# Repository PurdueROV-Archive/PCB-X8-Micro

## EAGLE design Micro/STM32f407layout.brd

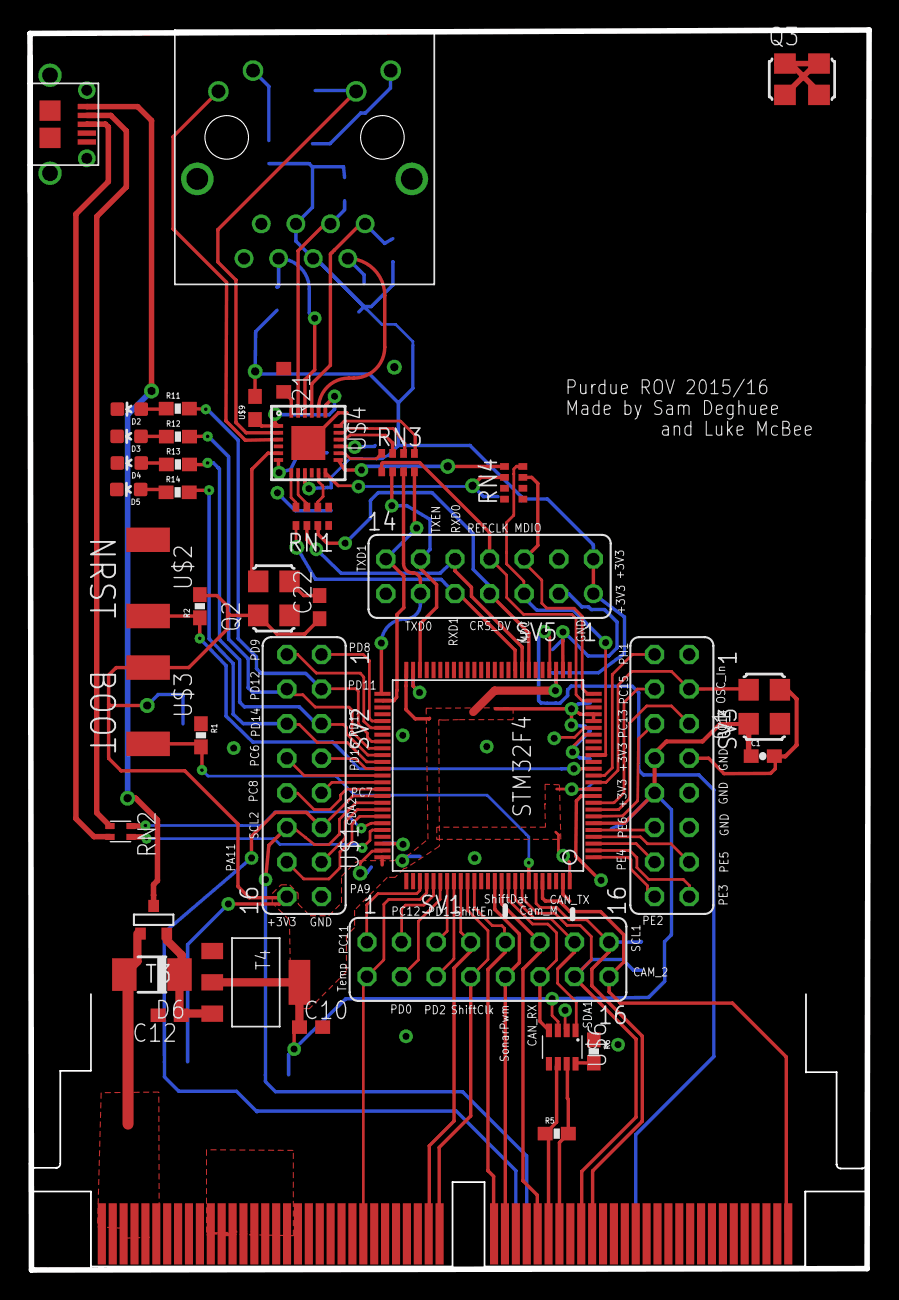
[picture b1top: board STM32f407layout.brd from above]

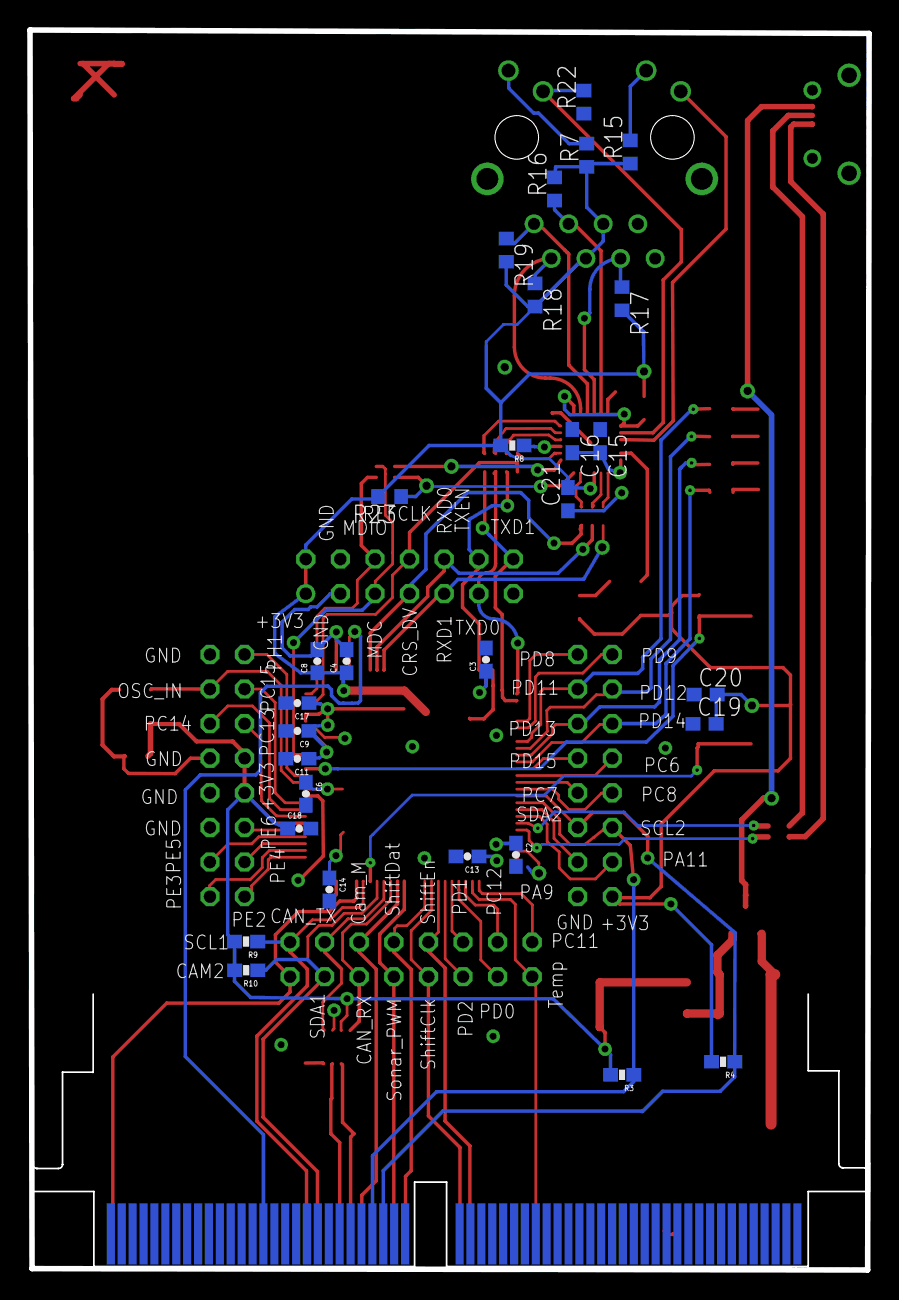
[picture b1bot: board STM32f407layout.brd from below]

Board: 2 copper layers, 61.6 x 91.0 mm, 69 parts (29 on the bottom side), 93 nets.

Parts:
C1: 0603-CAP
C2, C3: 0.22uF; 0603-CAP
C4, C6, C9, C11, C13, C14, C18: 0.1uF; 0603-CAP
C8: 4.7uF; 0603-CAP
C10, C12: 0.22uF; C0603
C15: 1uF; C0603
C16: 1nF; C0603
C17: 1uF; 0603-CAP
C19, C20, C21: 100nF; C0603
C22: 0.01uF; C0603
D2, D3, D4, D5: LED-0603
D6: DO-214AC
Q1, Q3: ASF
Q2: ASV-8; ASF
R1, R2: 10k; 0603-RES
R3, R4, R9, R10: 4.7K; 0603-RES
R5: 120; 0603-RES
R6: 100K; 0603-RES
R7, R15: 250R; R0603
R8: 10K; 0603-RES
R11, R12, R13, R14: 83; 0603-RES
R16, R17, R18, R19: 49.9R; R0603
R21: 12.1K; R0603
R22: 4.7K; R0603
R23: 1.5k; R0603
RN1, RN3, RN4: CAY16
RN2: EXBV4V
SV1, SV2, SV3: FE08-2
SV5: FE07-2
T3: FDN340P; SOT-23
T4: AP1117_LIN_REG; SOT223
U$1: STM32F4; LQFP100
U$2, U$3: SWITCH; SW_2512
U$4: LAN8720LAN8720; 24-QFN
U$5: MICROUSB; MICRO_B
U$6: MAX3051MAX3051; SOT23-8L
U$7: J00-0065NL
U$8: HSC8PART-60; HSC8-60PINOUUT
U$9: 0603

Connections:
+3V3: C1.1, C4.1, C6.1, C8.1, C9.1, C10.1, C11.1, C13.1, C14.1, C17.1, C18.1, C19.2, C20.2, C21.2, C22.1, Q1.4, Q2.4, R2.2, R3.2, R4.2, R7.1, R8.2, R9.2, R10.2, R15.1, R16.2, R17.2, R18.2, R19.2, R23.2, SV2.16, SV3.8, SV3.10, SV5.1, SV5.2, T4.TAB, T4.VOUT, U$1.P6, U$1.P11, U$1.P19, U$1.P21, U$1.P22, U$1.P28, U$1.P50, U$1.P75, U$1.P100, U$3.1, U$4.9, U$6.3, U$7.4, U$7.5, U$9.2
+5V: D6.A, T3.3, U$8.T1, U$8.T2, U$8.T3, U$8.T4, U$8.T5, U$8.T6
ALT_CAMERA_SERVO_MOTOR_PWM: SV1.16, U$1.P96, U$8.T60
BUS_SPEED: R22.2, U$4.2, U$7.10
CANH1: R5.2, U$6.7, U$8.T39
CANL1: R5.1, U$6.6, U$8.T38
CAN_RX: SV1.12, U$1.P91, U$6.4
CAN_TX: SV1.13, U$1.P92, U$6.1
CRS_DV: RN1.3, SV5.7, U$1.P32
DIFF_RD+: R16.1, U$4.23, U$7.3
DIFF_RD-: R17.1, U$4.22, U$7.6
DIFF_TD+: R19.1, U$4.21, U$7.1
DIFF_TD-: R18.1, U$4.20, U$7.2
GND: C1.2, C2.2, C3.2, C4.2, C6.2, C8.2, C9.2, C10.2, C11.2, C12.2, C13.2, C14.2, C15.1, C16.1, C17.2, C18.2, C19.1, C20.1, C21.1, C22.2, D2.C, D3.C, D4.C, D5.C, Q1.2, Q2.2, R1.1, R6.1, R21.1, R22.1, SV2.15, SV3.1, SV3.7, SV3.9, SV3.11, SV5.3, SV5.4, T4.GND, U$1.P10, U$1.P20, U$1.P27, U$1.P74, U$1.P99, U$2.1, U$4.VSS_PAD, U$5.GND1, U$5.GND2, U$5.GND3, U$5.GND4, U$5.GND7, U$5.GND8, U$5.P4, U$5.P5, U$6.2, U$7.8, U$7.15, U$7.16, U$8.T11, U$8.T12, U$8.T13, U$8.T14, U$8.T15, U$8.T16, U$8.T17, U$8.T18
GREEN: R7.2, U$7.9
I2C1_SCL: R9.1, SV1.15, U$1.P95, U$8.T42
I2C1_SDA: R10.1, SV1.14, U$1.P93, U$8.T41
I2C3_SCL: R3.1, SV2.12, U$1.P67, U$8.B36
I2C3_SDA: R4.1, SV2.11, U$1.P66, U$8.B35
LINK/ACT: U$4.3, U$7.12
MAIN_CAMERA_SERVO_MOTOR_PWM: SV1.11, U$1.P90, U$8.T37
MDC: RN4.8, SV5.5, U$1.P16
MDE: RN4.1, U$4.13
MDIO: RN4.7, SV5.6, U$1.P25
unnamed: C2.1, U$1.P73
unnamed: C3.1, U$1.P49
unnamed: R1.2, U$1.P94, U$3.2
unnamed: R2.1, U$1.P14, U$2.2
unnamed: C15.2, C16.2, U$4.6
unnamed: RN1.6, U$4.11
unnamed: R6.2, U$6.8
unnamed: RN2.1, U$5.P2
unnamed: RN3.4, U$4.14
unnamed: D3.A, R12.1
unnamed: D5.A, R14.1
unnamed: RN3.3, U$4.16
unnamed: D4.A, R13.1
unnamed: D2.A, R11.1
unnamed: RN3.2, U$4.17
unnamed: RN3.1, U$4.18
unnamed: U$4.1, U$4.19, U$9.1
unnamed: R21.2, U$4.24
unnamed: R23.1, RN4.2, U$4.12
unnamed: RN2.2, U$5.P3
unnamed: RN1.7, U$4.8
unnamed: RN1.8, U$4.7
unnamed: Q3.1, Q3.2, Q3.3, Q3.4
unnamed: T3.1, U$5.P1
unnamed: C12.1, D6.C, T3.2, T4.VIN
NRST: R8.1, U$4.15
OSC_IN: Q1.3, SV3.3, U$1.P12
PA9: SV2.13, U$1.P68
PA10: SV2.14, U$1.P69
PC6: SV2.8, U$1.P63
PC7: SV2.9, U$1.P64
PC8: SV2.10, U$1.P65
PC10: SV1.1, U$1.P78
PC12: SV1.3, U$1.P80
PC13: SV3.6, U$1.P7
PC14: SV3.5, U$1.P8
PC15: SV3.4, U$1.P9
PD0: SV1.4, U$1.P81
PD1: SV1.5, U$1.P82
PD2: SV1.6, U$1.P83
PD8: SV2.1, U$1.P55
PD9: SV2.2, U$1.P56
PD11: R11.2, SV2.3, U$1.P58
PD12: R12.2, SV2.4, U$1.P59
PD13: R13.2, SV2.5, U$1.P60
PD14: R14.2, SV2.6, U$1.P61
PD15: SV2.7, U$1.P62
PE2: SV3.16, U$1.P1
PE3: SV3.15, U$1.P2
PE4: SV3.14, U$1.P3
PE5: SV3.13, U$1.P4
PE6: SV3.12, U$1.P5
PH1: SV3.2, U$1.P13
REFCLK: RN3.5, SV5.8, U$1.P24
RXD0: RN1.2, SV5.10, U$1.P33
RXD1: RN1.1, SV5.9, U$1.P34
SHIFTREG_CLK: SV1.8, U$1.P85, U$8.T32
SHIFTREG_DATA: SV1.9, U$1.P86, U$8.T33
SHIFTREG_ENABLE: SV1.7, U$1.P84, U$8.T31
SONAR_DAC: U$1.P29, U$8.B46
SONAR_PWM: SV1.10, U$1.P89, U$8.T34
TEMP_BACKUP: SV1.2, U$1.P79, U$8.T25
TXD0: RN3.7, SV5.11, U$1.P51
TXD1: RN3.8, SV5.14, U$1.P52
TXEN: RN3.6, SV5.12, U$1.P48
USB_D+: RN2.3, U$1.P71
USB_D-: RN2.4, U$1.P70
XTAL1: Q2.3, U$4.5
YELLOW: R15.2, U$7.11

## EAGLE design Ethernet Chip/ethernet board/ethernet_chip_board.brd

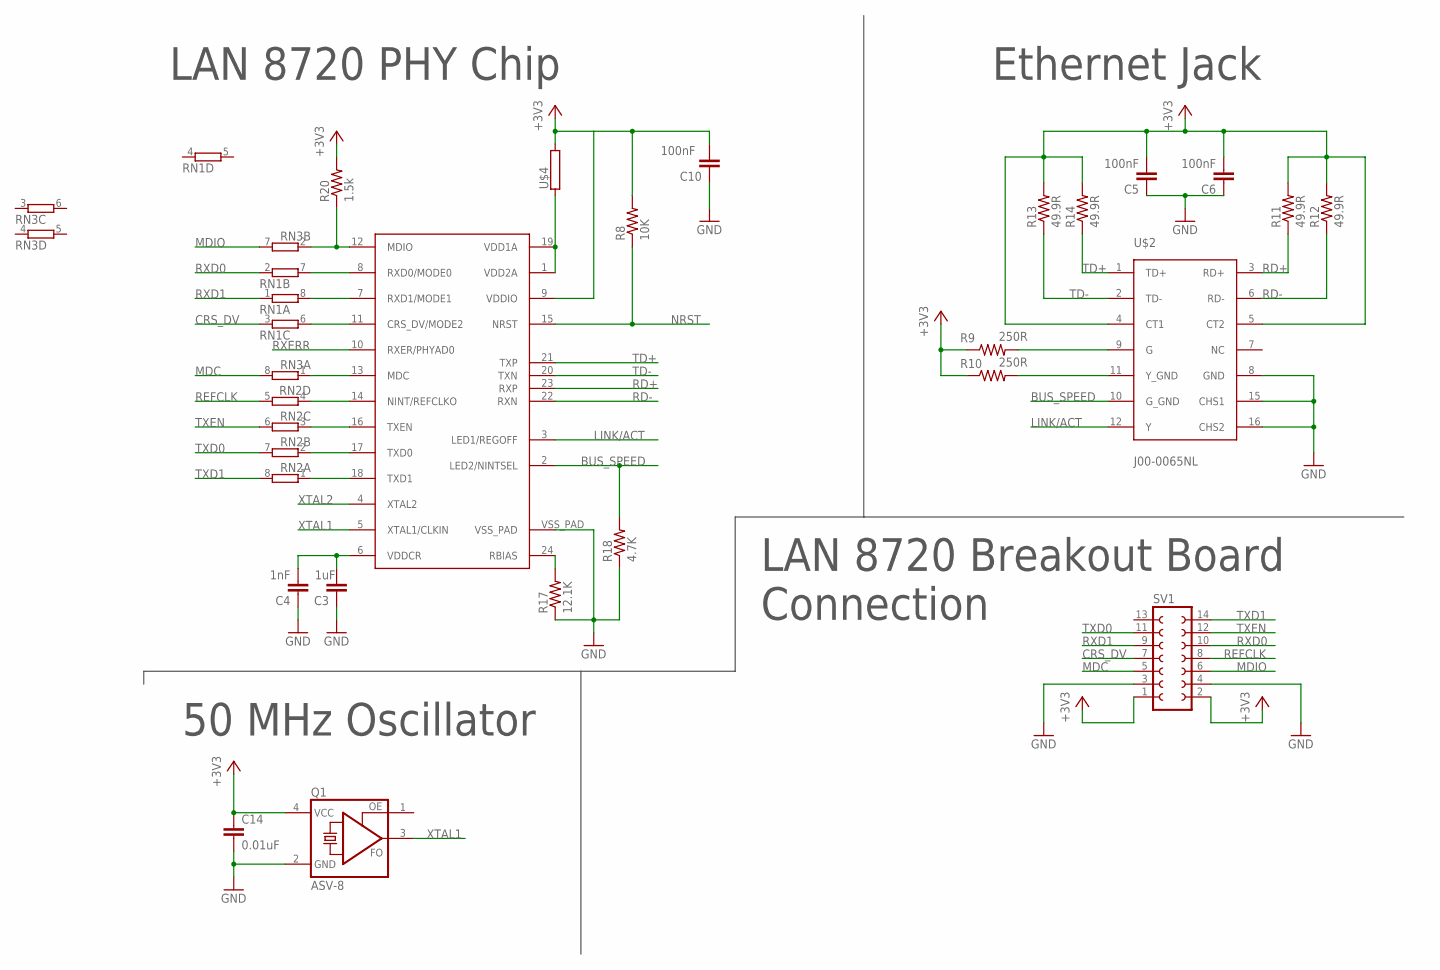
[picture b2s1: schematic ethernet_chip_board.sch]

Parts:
C3: 1uF; C0603
C4: 1nF; C0603
C5, C6, C10: 100nF; C0603
C14: 0.01uF; C0603
Q1: ASV-8; ASF
R8: 10K; 0603-RES
R9, R10: 250R; R0603
R11, R12, R13, R14: 49.9R; R0603
R17: 12.1K; R0603
R18: 4.7K; R0603
R20: 1.5k; R0603
RN1, RN2, RN3: 4R-NCAY16; CAY16
SV1: FE07-2
U$1: LAN8720LAN8720; 24-QFN
U$2: J00-0065NL
U$4: 553-2382-1-ND; 0603

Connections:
+3V3: C5.2, C6.2, C10.2, C14.1, Q1.4 (VCC), R8.2, R9.1, R10.1, R11.2, R12.2, R13.2, R14.2, R20.2, SV1.1, SV1.2, U$1.9 (VDDIO), U$2.4 (CT1), U$2.5 (CT2), U$4.2
BUS_SPEED: R18.2, U$1.2 (LED2/NINTSEL), U$2.10 (G_GND)
CRS_DV: RN1.3 (1), SV1.7
GND: C3.1, C4.1, C5.1, C6.1, C10.1, C14.2, Q1.2 (GND), R17.1, R18.1, SV1.3, SV1.4, U$1.VSS_PAD, U$2.8 (GND), U$2.15 (CHS1), U$2.16 (CHS2)
GREEN: R9.2, U$2.9 (G)
LINK/ACT: U$1.3 (LED1/REGOFF), U$2.12 (Y)
MDC: RN3.8 (2), SV1.5
MDE: RN3.1, U$1.13 (MDC)
MDIO: RN3.7 (2), SV1.6
unnamed: RN1.7 (2), U$1.8 (RXD0/MODE0)
unnamed: RN1.8 (2), U$1.7 (RXD1/MODE1)
unnamed: C3.2, C4.2, U$1.6 (VDDCR)
unnamed: R17.2, U$1.24 (RBIAS)
unnamed: RN1.6 (2), U$1.11 (CRS_DV/MODE2)
unnamed: RN2.4 (1), U$1.14 (NINT/REFCLKO)
unnamed: RN2.3 (1), U$1.16 (TXEN)
unnamed: RN2.2 (1), U$1.17 (TXD0)
unnamed: RN2.1, U$1.18 (TXD1)
unnamed: U$1.1 (VDD2A), U$1.19 (VDD1A), U$4.1
unnamed: R20.1, RN3.2 (1), U$1.12 (MDIO)
NRST: R8.1, U$1.15 (NRST)
RD+: R11.1, U$1.23 (RXP), U$2.3 (RD+)
RD-: R12.1, U$1.22 (RXN), U$2.6 (RD-)
REFCLK: RN2.5 (2), SV1.8
RXD0: RN1.2 (1), SV1.10
RXD1: RN1.1, SV1.9
RXERR: U$1.10 (RXER/PHYAD0)
TD+: R14.1, U$1.21 (TXP), U$2.1 (TD+)
TD-: R13.1, U$1.20 (TXN), U$2.2 (TD-)
TXD0: RN2.7 (2), SV1.11
TXD1: RN2.8 (2), SV1.14
TXEN: RN2.6 (2), SV1.12
XTAL1: Q1.3 (FO), U$1.5 (XTAL1/CLKIN)
XTAL2: U$1.4 (XTAL2)
YELLOW: R10.2, U$2.11 (Y_GND)

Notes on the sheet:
Ethernet Jack
LAN 8720 PHY Chip
50 MHz Oscillator
LAN 8720 Breakout Board Connection

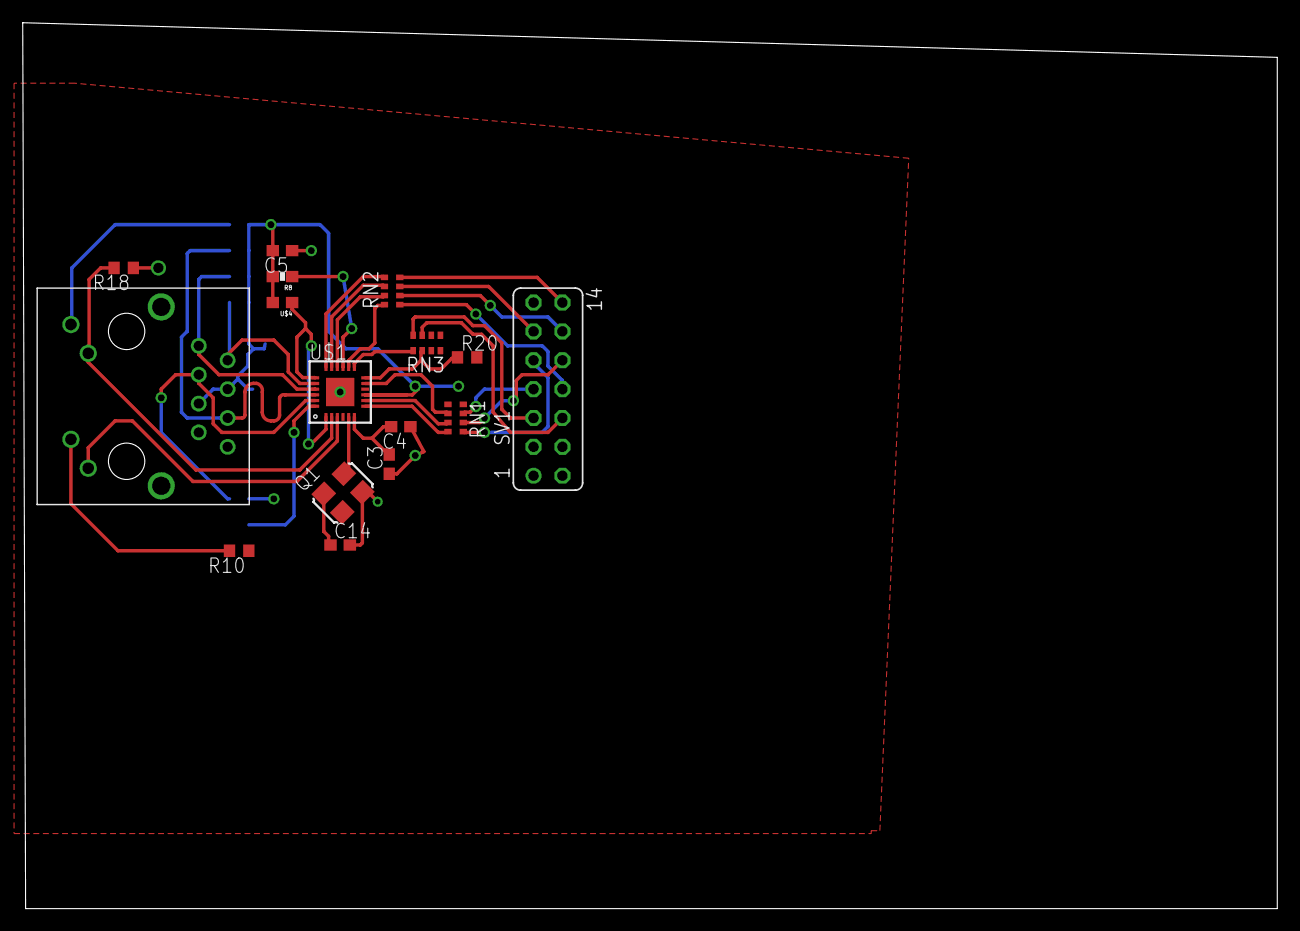
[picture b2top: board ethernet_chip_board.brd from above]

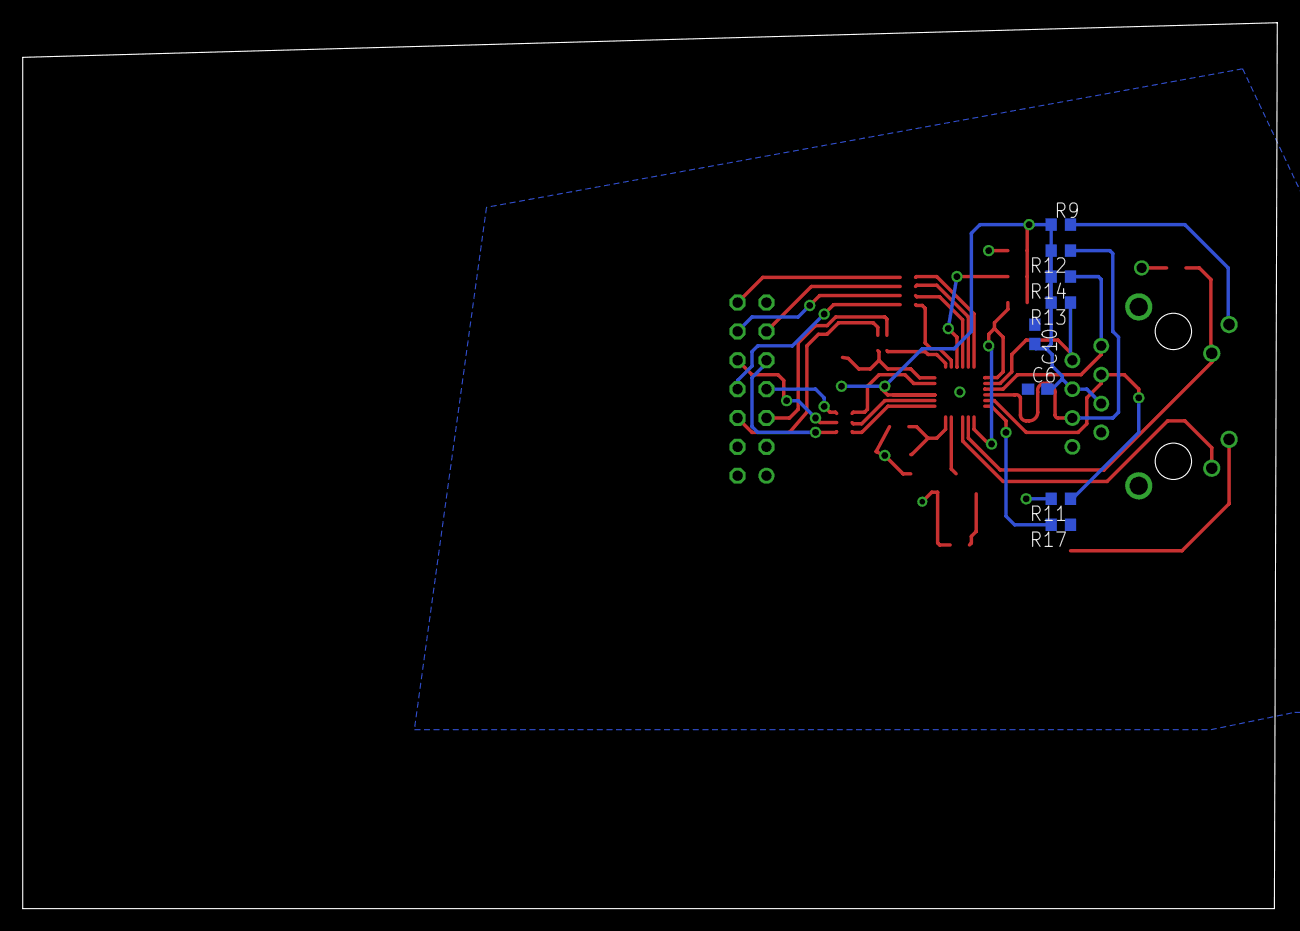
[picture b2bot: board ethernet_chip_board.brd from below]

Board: 2 copper layers, 110.4 x 78.0 mm, 24 parts (8 on the bottom side), 33 nets.

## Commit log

2015-10-24 Created part for LAN8720 in Eagle.
2015-10-24 Created LAN8720 part in Eagle.
    This library contains a dot indicating the position of the first pin.
    This dot was not present in the previous version.
2015-10-31 Updated Ethernet Chip Library
2015-11-08 Fixed folders
2015-11-11 Next Step for Power, tied I2C high
    Next step in micro board schematic
2015-11-14 Updated Ethernet Schematic (From Paul)
2015-11-14 Updated Ethernet Schematic (Paul)
2015-11-15 Cleaned up microboard folder
2015-11-15 "Cleaned up the ethernet chip schematic"
2015-11-15 Finished the ethernet board schematic
2015-11-15 Cleaned up the lan8720 schematic
2015-11-18 Pushed latest updates
    Added labels and buttons for boot and such
2015-11-19 Started Ethernet Board Layout
2015-11-23 Worked on the board layout for the ethernet circuit
2015-11-25 Update on more parts
    Whooo Updates
2015-11-26 Worked on List that Luke and I worked on
    Includes, almost set up USB, LEDs, Almost a power Supply, CAN Chip
    Connections and More!
2015-11-30 Finished Power Layout, added pin header, added USB
    finished list from Luke/Sam Conversation
2015-12-03 updated the ethernet board
2015-12-04 Added some of needed additional circuits
2015-12-04 Final Version before Design Review
    Fixed Pin Out Problems
2015-12-05 "Fixed saving problems"
2015-12-05 "Added 50 MHz Oscillator"
2015-12-07 Trying to fix permissions issure
2015-12-07 Fixing a bug
2015-12-07 Still trying to fix saving issue
2015-12-07 fixing some more bugs
2015-12-07 fixing the locked files
2015-12-10 Began Board Layout
2015-12-10 worked on board layout, set initial width requirements
2015-12-16 Updated Board
2015-12-16 More Board Updates
    Remind myself to switch LED pins
2015-12-19 Made changes to the micro board
2015-12-20 Updated Board on flight
    moved TXD0 pin connection to not cross transmission lines
    remove PC0 so can run MDC out. If it is a clock its pretty important
    that it does not go under micro
    may want to move xtal, bit far away probably wont be a problem but hf
    signals do not like distance and things inbetween them
    check via usage, use different ones , may want to stick to 1 size
2015-12-21 Holiday Update 1
    Connected extra capacitors, changed PC0 to GND for now, May route to
    better pinout later. Added GND planes made sure no unrouted
2015-12-27 Ethernet Addition
    I added the ethernet chip and added essential routes, need to do
    tolerance checks
2015-12-27 Ethernet Length Checks
    Checked length of ethernet signals, still need to check tolerances on
    RD+- and TD+-
2015-12-27 More Updates
    Moved ehternet jack, made things similar in length
2015-12-28 Other Update
    Updated power and ground, might need more fixing based on other traces.
    need to check if can use different pins for Sonar PWM and DAC, as well
    as Servo PWMs.
2015-12-30 Added rough sketch for bottom pinout
2015-12-30 Fixed Polygons for Power and GND
2015-12-30 Moved final clearances
    Double Checked vias and trace distances
2015-12-30 added real header pin
    Did a rough draft of connections to backplane
2015-12-31 Imprved spacing, changed bottom pinouts
2016-01-01 Fixed DRC Errors, Began fixing other problems
2016-01-03 Fixed some wiring on the microboard
2016-01-03 Cleaned up the board
2016-01-05 Added Silkscreen Pin labels
2016-01-06 Updated Silkscreen
2016-01-16 Update to fix information from "final" design review
    moved micro usb connector, fixed power square
2016-01-16 Finished changes for trying to fix micro board
    Last push of integrated ethernet
2016-01-21 Working on getting Eagle Up to work

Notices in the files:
parts and their libraries:
SparkFun-Passives: Licensing: Creative Commons ShareAlike 4.0 International - https://creativecommons.org/licenses/by-sa/4.0
